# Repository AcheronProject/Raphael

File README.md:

# Acheron Raphael

## Introduction

Raphael is a gummy-mount 60% layout PCB supporting both an on-board USB connector and a JST for USB dautherboard connection.

For its full documentation, see [the AcheronDocs page on Raphael](https://acherondocs.com/pcbs/raphael/raphael)

## Copyright notice

This project is released under the Acheron Open-Hardware License V1.4. For the license, please refer to the LICENCE.md file.

The "angel with sword" logo was licensed through Vectorstock; the license does not allow for redistribution so the source file is not available. The license was obtained in february 08, 2022 and allows for commercial usage of the logo, therefore allowing the PCBs to be used commercially.

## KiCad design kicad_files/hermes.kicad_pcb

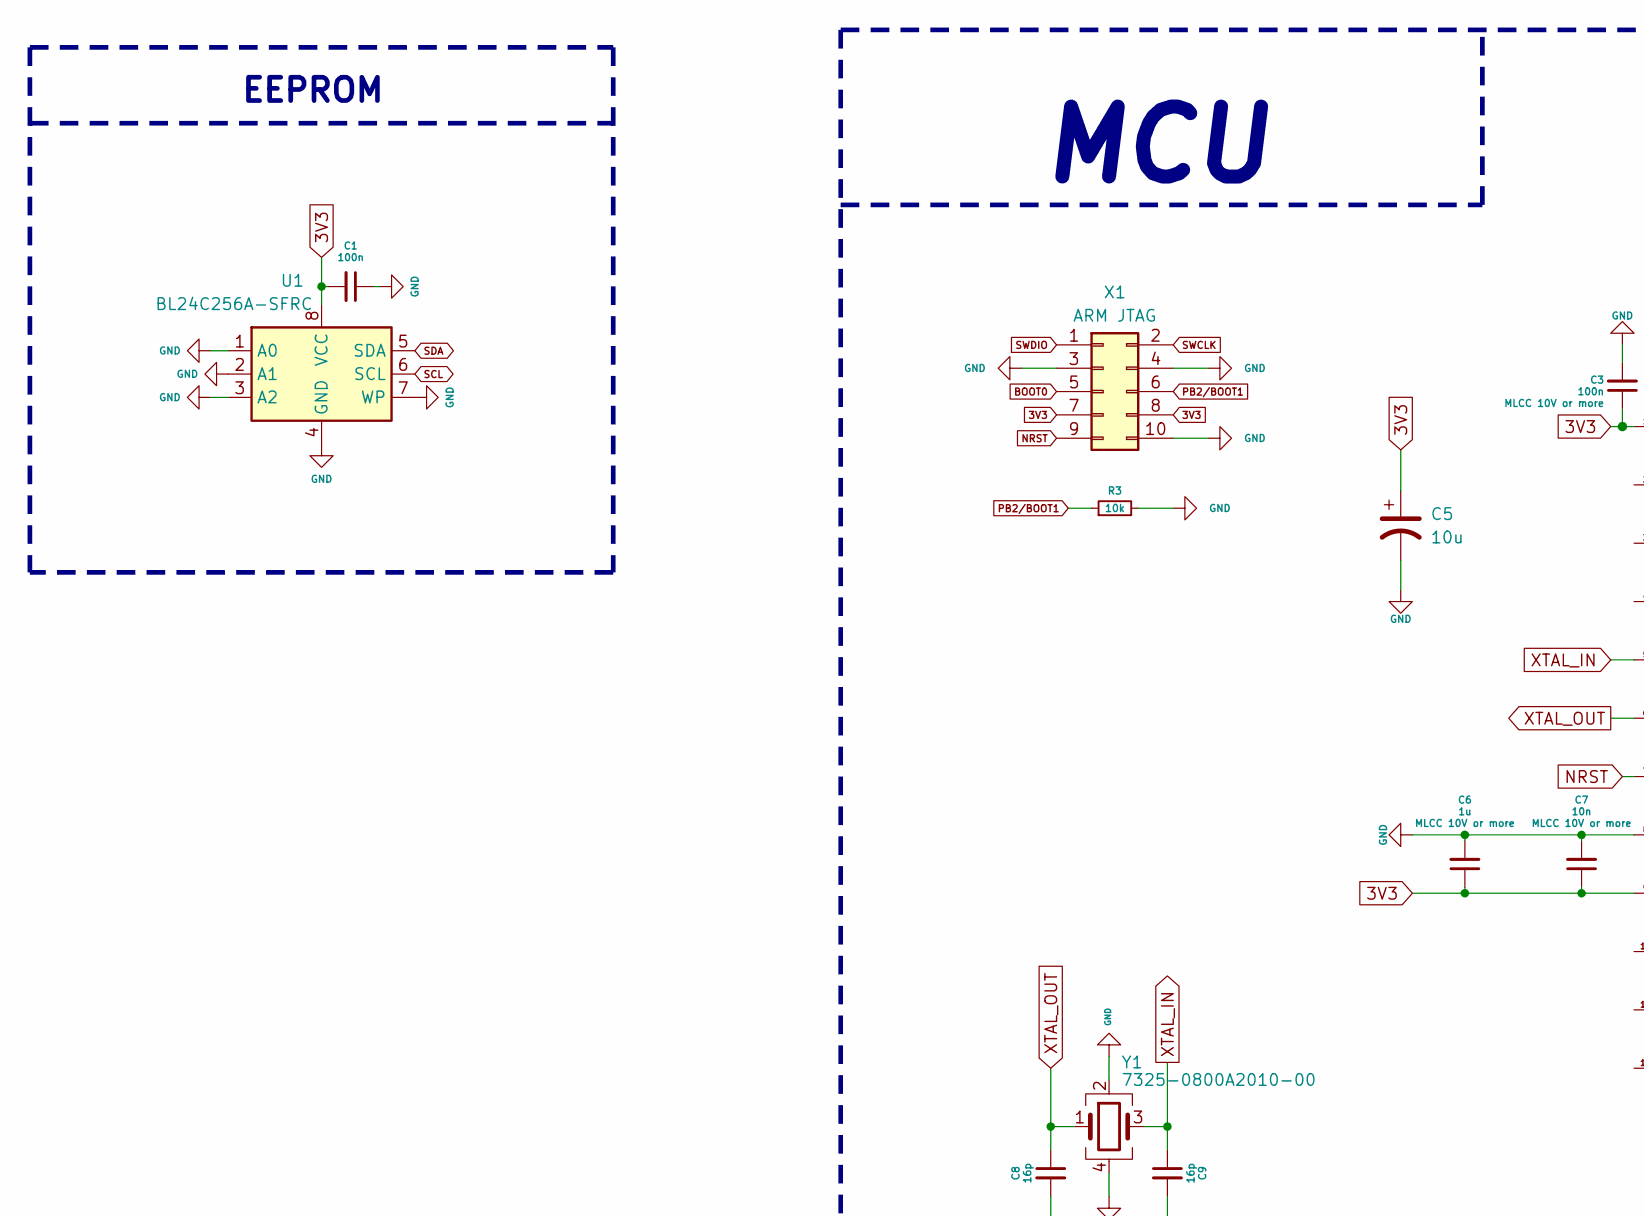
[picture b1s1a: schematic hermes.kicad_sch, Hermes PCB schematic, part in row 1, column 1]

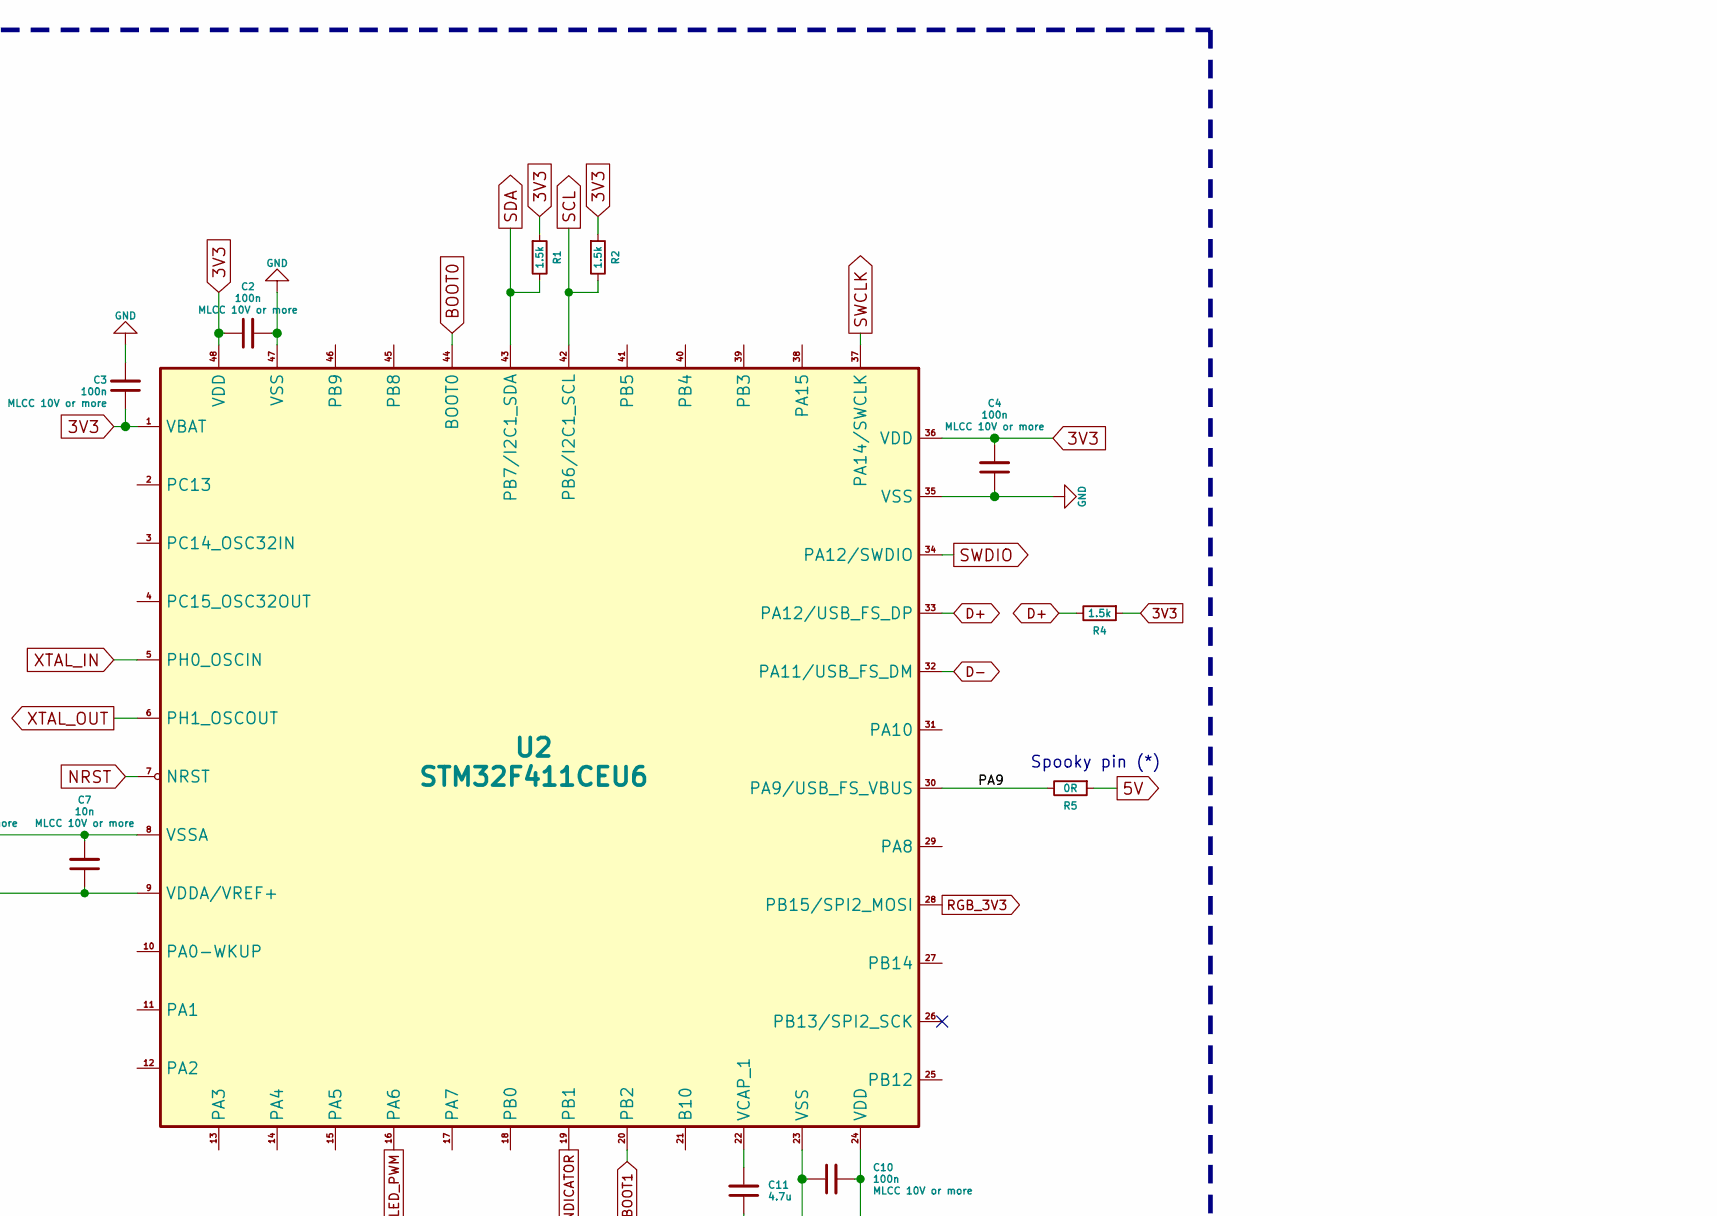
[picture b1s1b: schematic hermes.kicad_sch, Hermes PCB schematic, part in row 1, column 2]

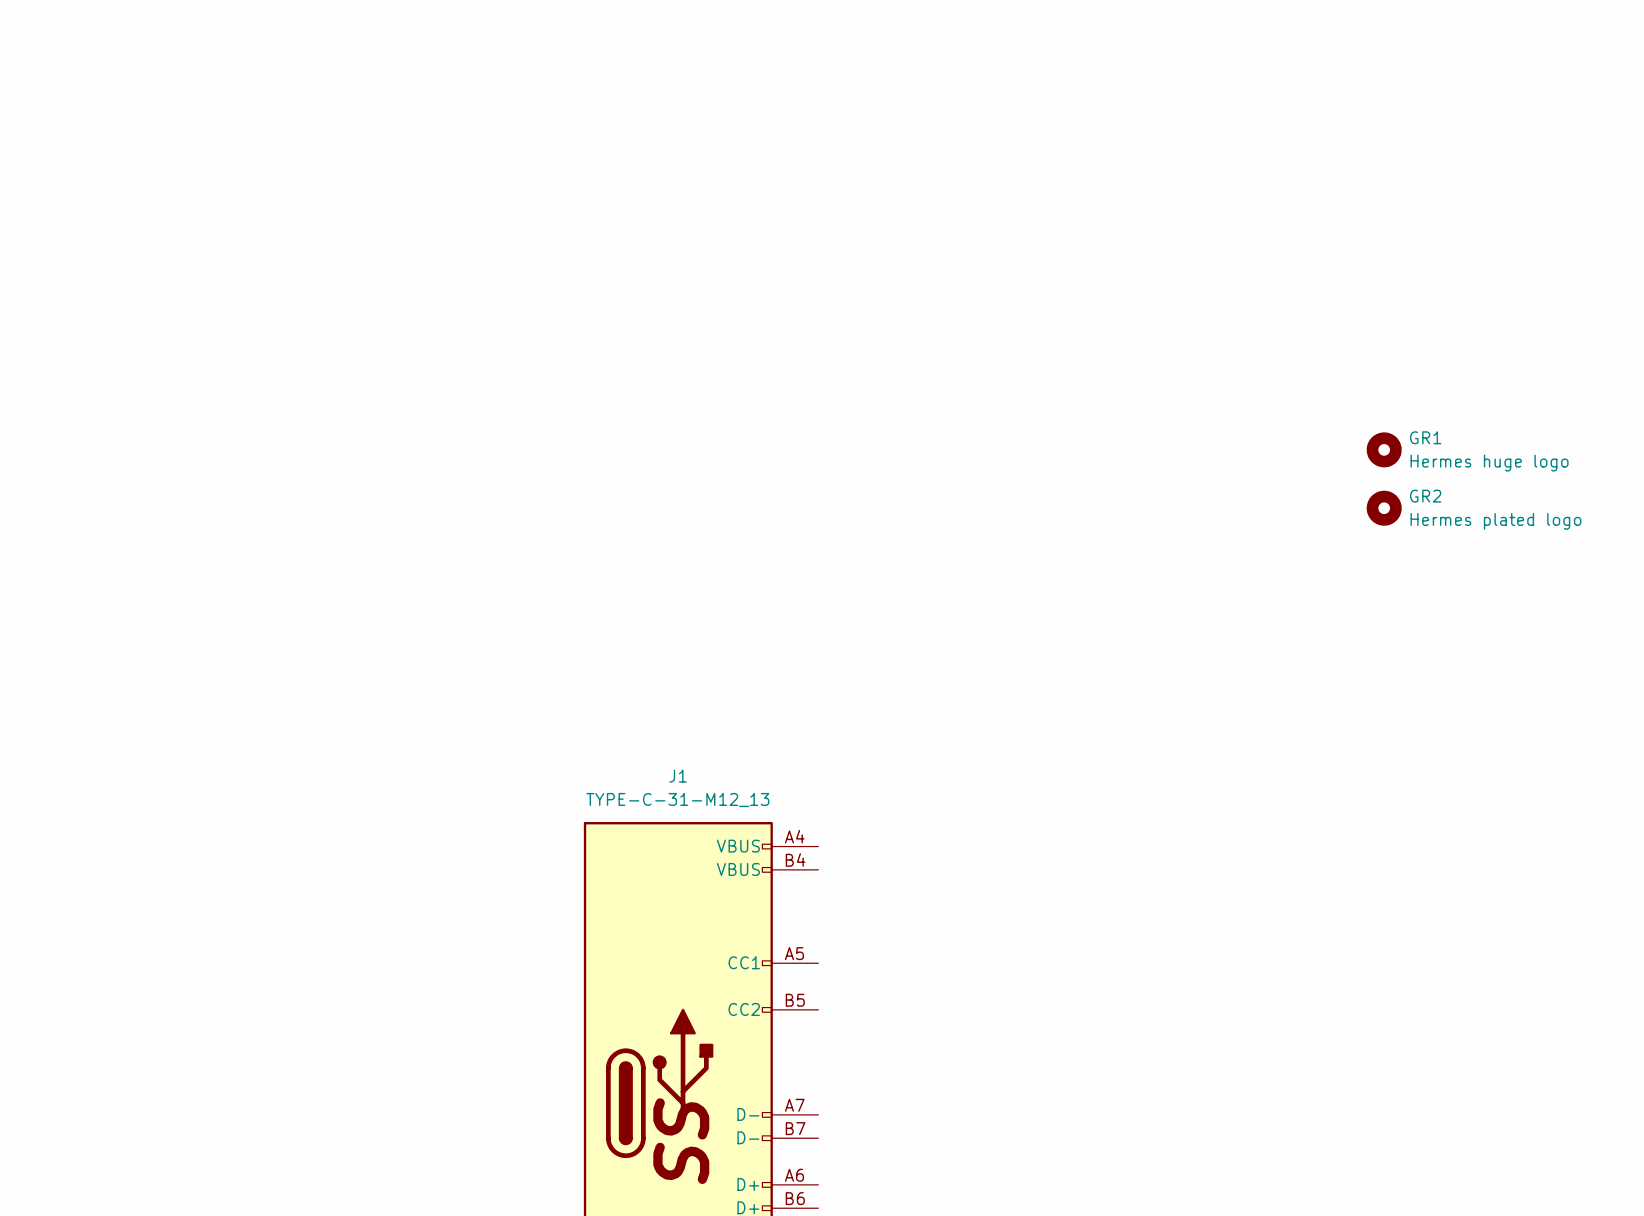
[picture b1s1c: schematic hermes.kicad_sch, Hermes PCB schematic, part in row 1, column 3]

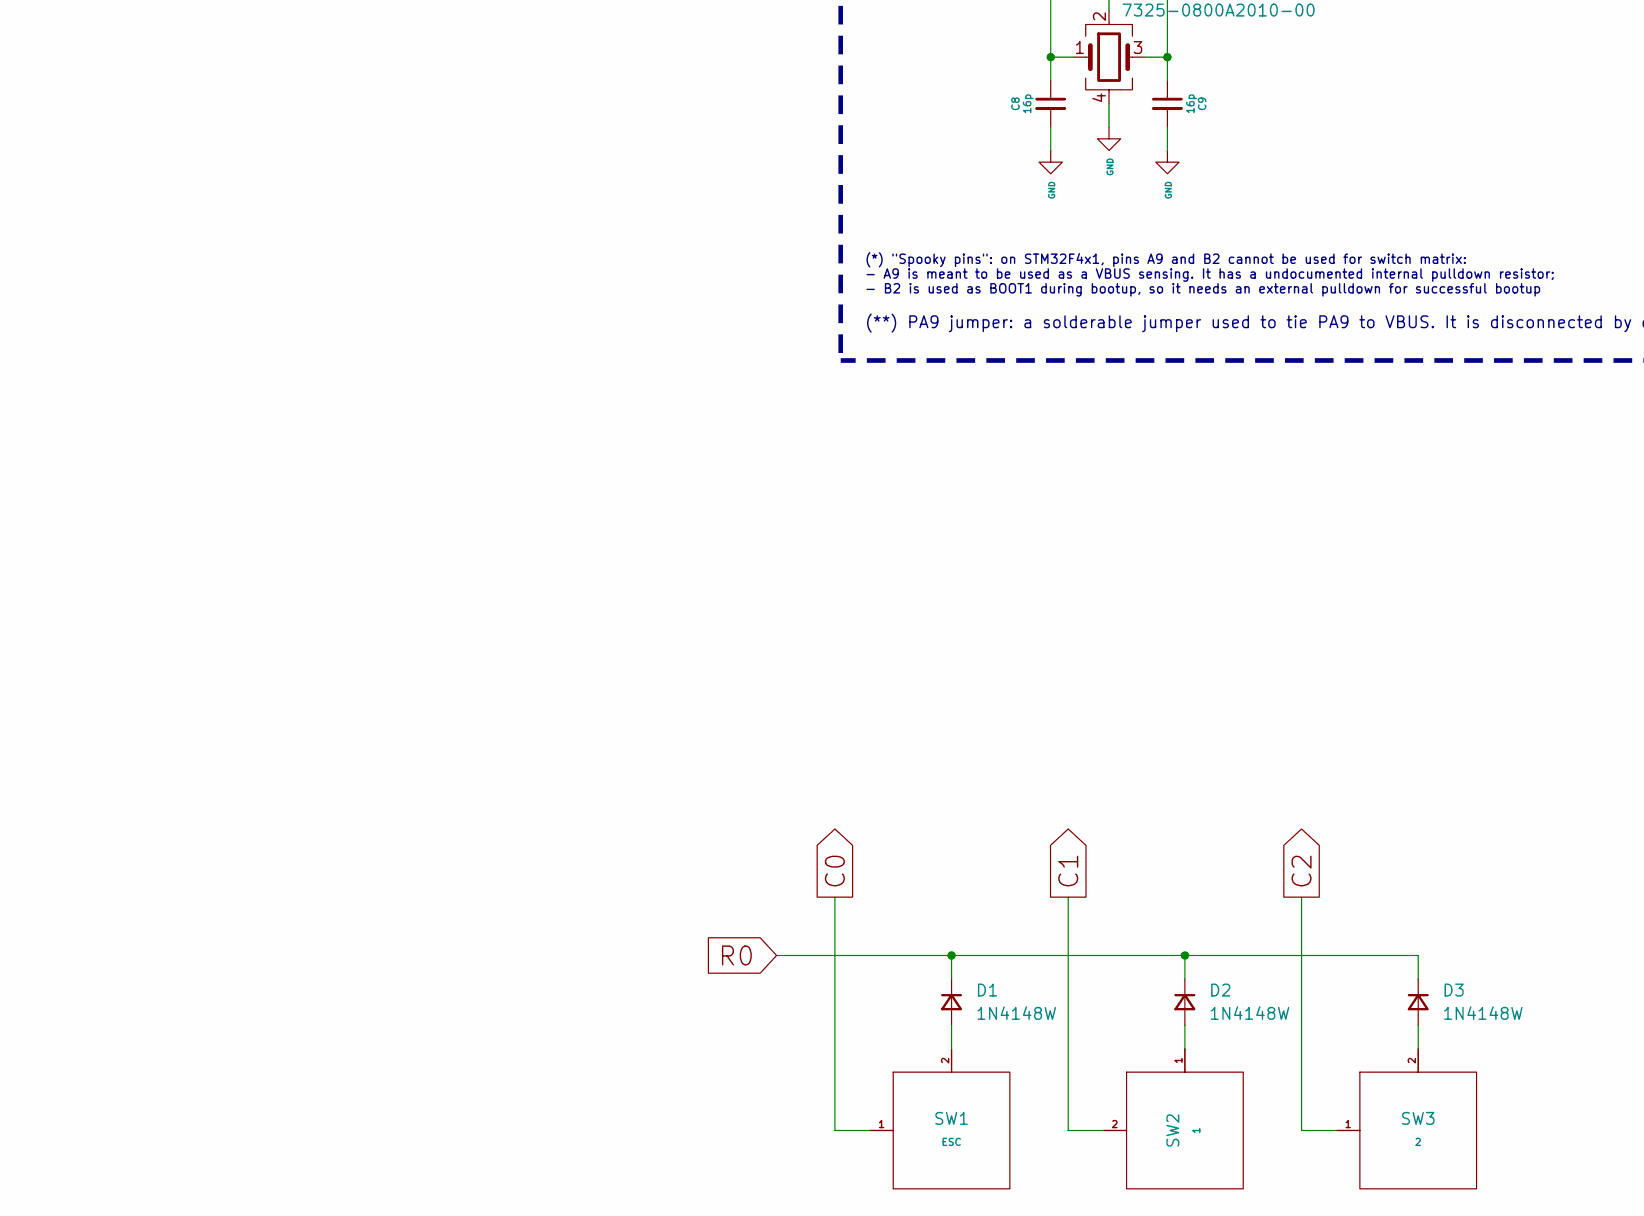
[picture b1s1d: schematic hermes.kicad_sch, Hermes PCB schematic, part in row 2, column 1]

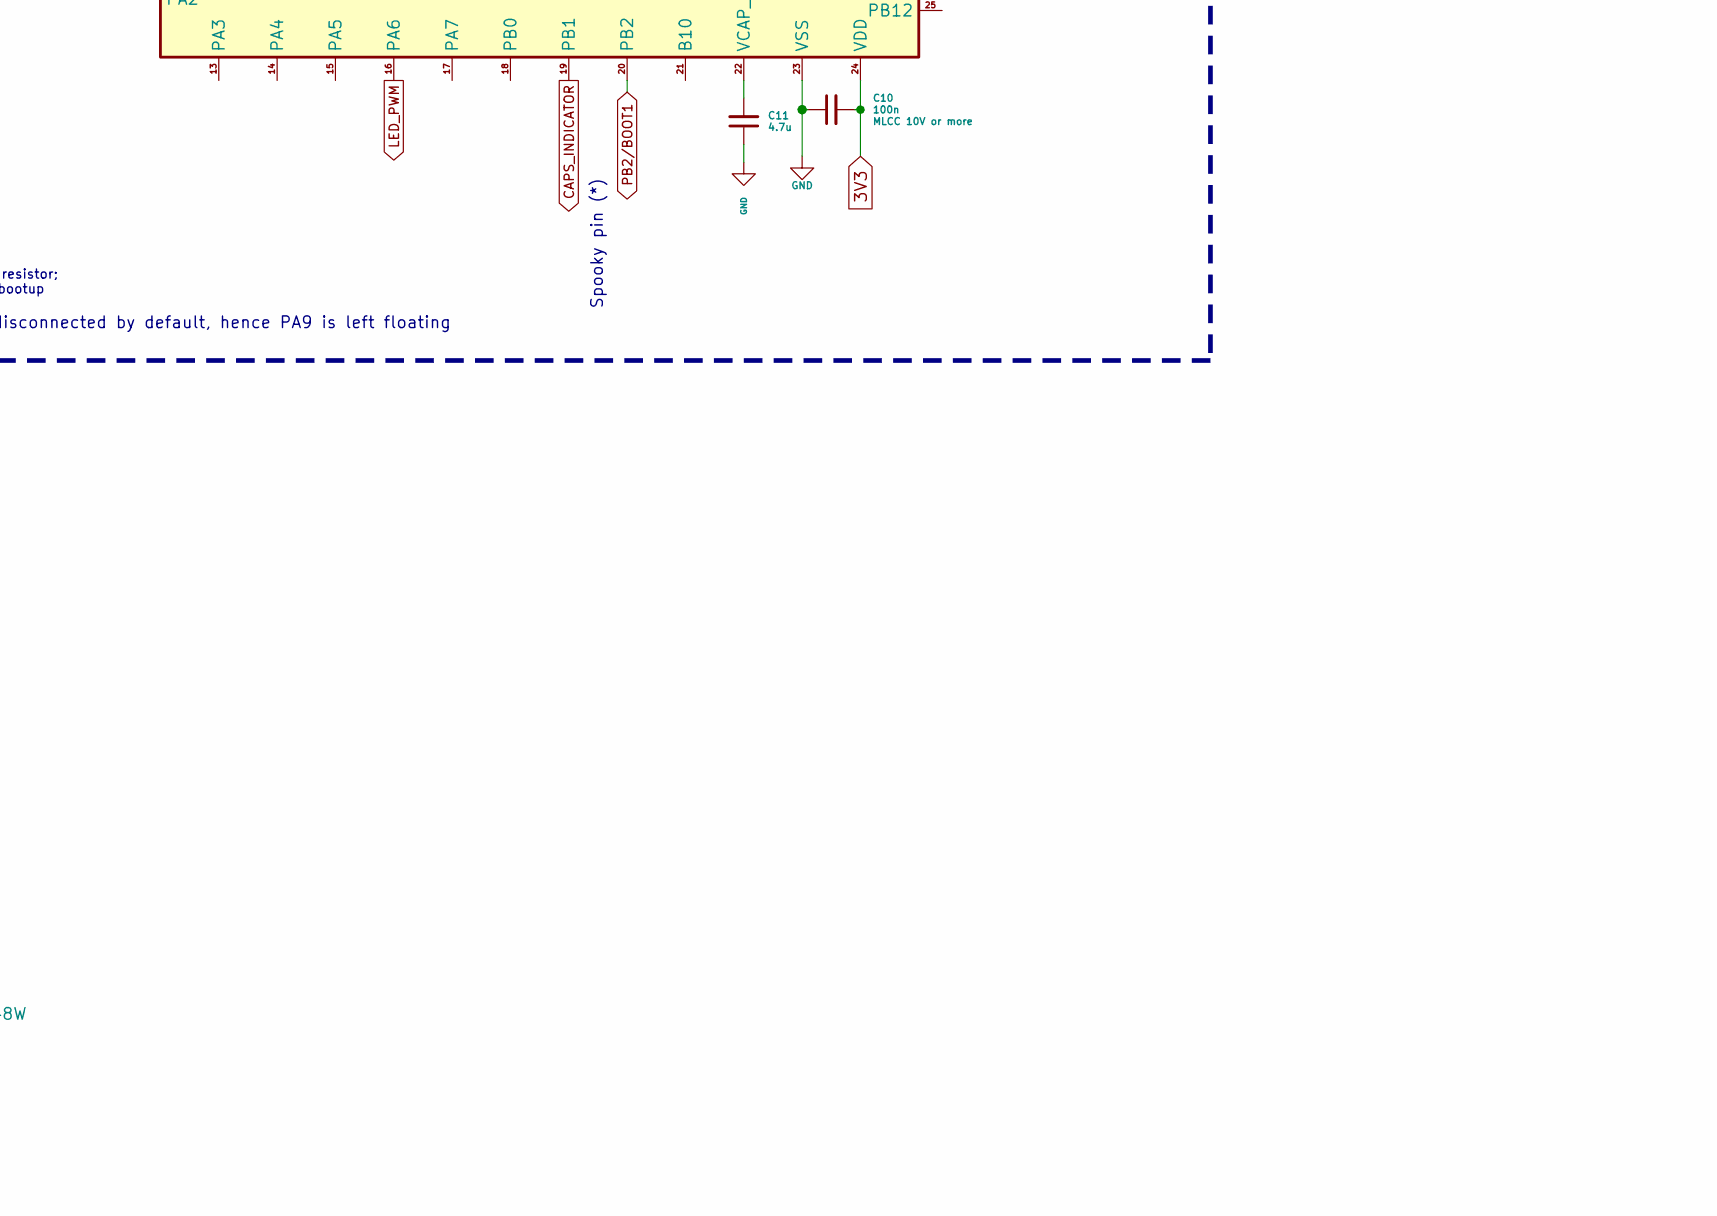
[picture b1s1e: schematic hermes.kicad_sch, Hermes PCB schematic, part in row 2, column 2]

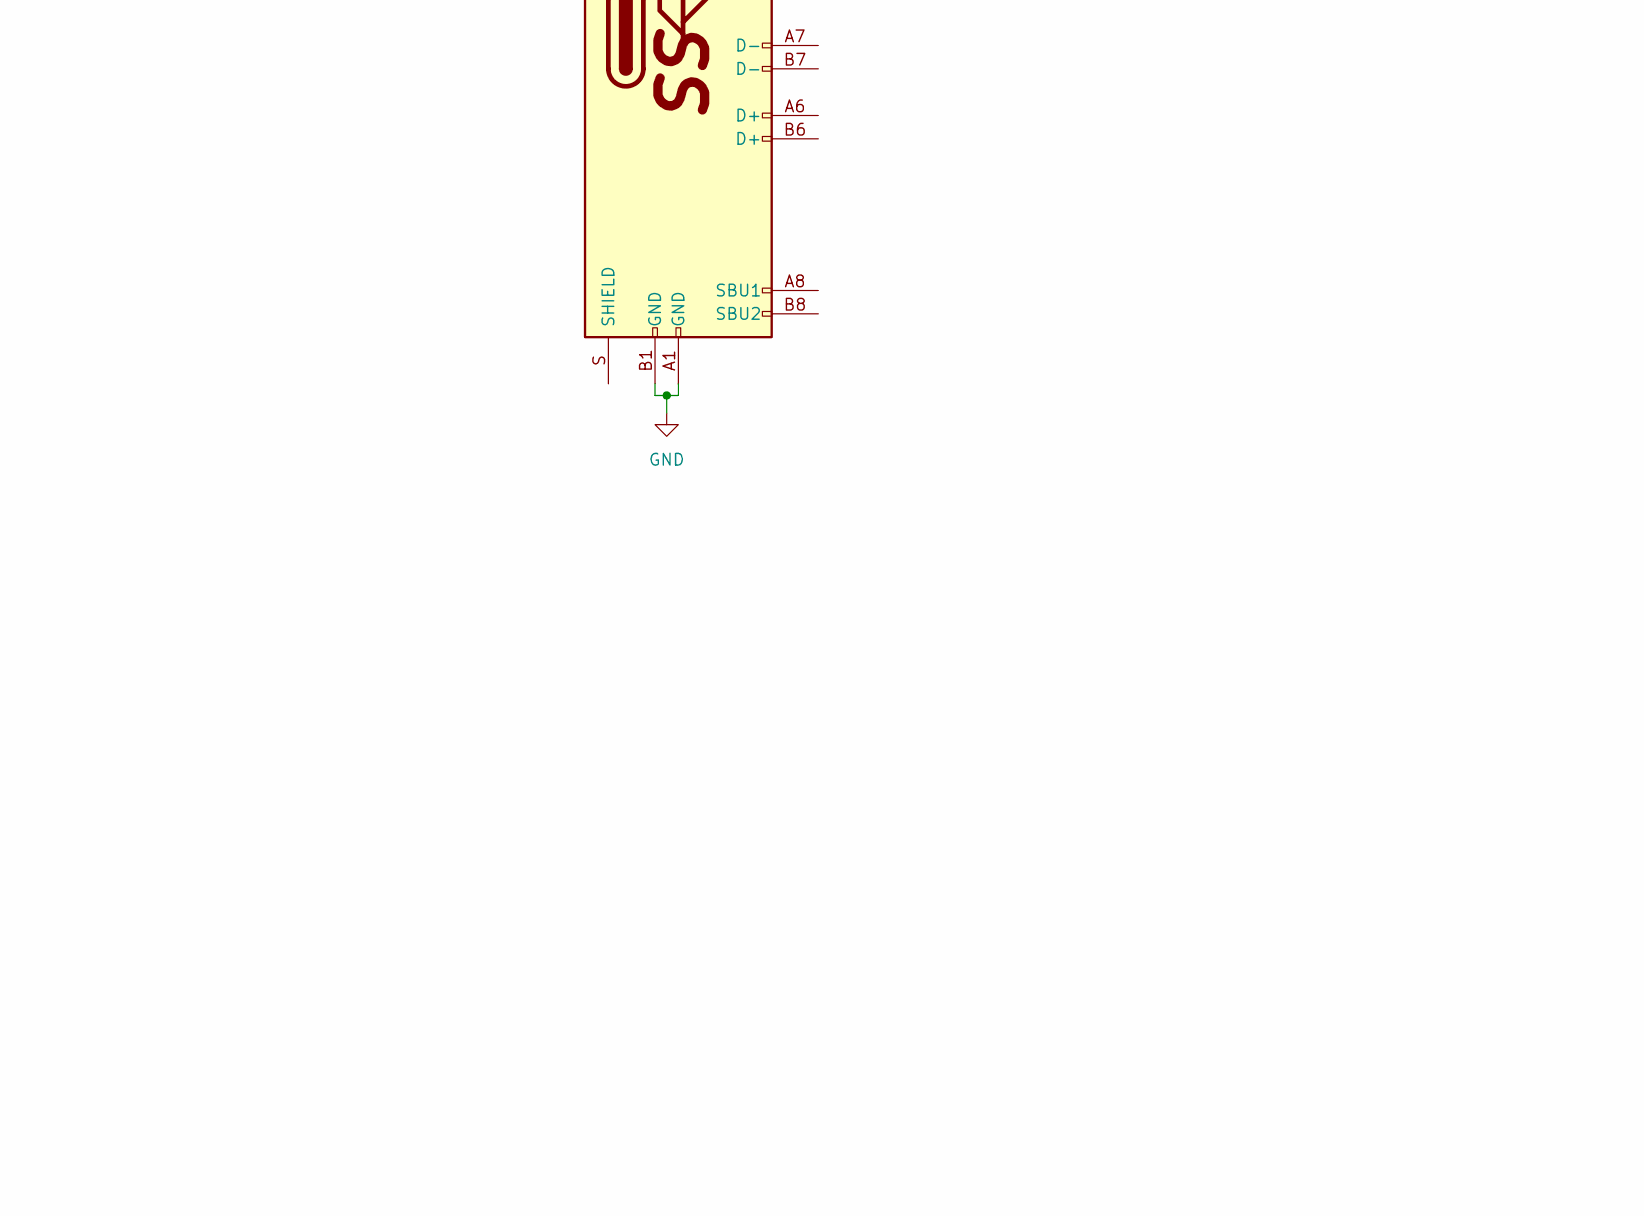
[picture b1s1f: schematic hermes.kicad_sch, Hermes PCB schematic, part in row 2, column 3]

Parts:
C1, C2, C3, C4, C10: 100n; C_0402_1005Metric
C5: 10u; CP_EIA-3216-10_Kemet-I_Pad1.58x1.35mm_HandSolder
C6: 1u; C_0402_1005Metric
C7: 10n; C_0402_1005Metric
C8, C9: 16p; C_0402_1005Metric
C11: 4.7u; C_0402_1005Metric
D1, D2, D3: 1N4148W; D_SOD-123; Manufacturer Part Number 1N4148W
GR1: Hermes huge logo; hermes_logo_56.9x84mm
GR2: Hermes plated logo; hermes_plated_logo_12x17.7mm
J1: TYPE-C-31-M12_13; TYPE-C-31-M-12
R1, R2, R4: 1.5k; R_0402_1005Metric
R3: 10k; R_0805_2012Metric
R5: 0R; R_0805_2012Metric
SW1, SW2, SW3: Mechanical_Switch; MX100
U1: BL24C256A-SFRC; TSSOP-8_4.4x3mm_P0.65mm; Manufacturer Part Number BL24C256A-SFRC
U2: STM32F411CEU6; STM_UFQFPN-48_LQFP-48-1EP_7x7mm_P0.5mm_HandSoldering_Therma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; Manufacturer Part Number STM32F411
X1: ARM JTAG; PinHeader_2x5_P2.54mm_Vertical_Staggered
Y1: 7325-0800A2010-00; Crystal_SMD_3225-4Pin_3.2x2.5mm; Manufacturer Part Number 7325-0800A2010-00

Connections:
3V3: C1.2, C2.1, C3.1, C4.2, C5.1, C6.1, C7.1, C10.2, R1.1, R2.1, R4.1, U1.8 (VCC), U2.1 (VBAT), U2.9 (VDDA/VREF+), U2.24 (VDD), U2.36 (VDD), U2.48 (VDD), X1.7, X1.8
5V: R5.1
/PA9: R5.2, U2.30 (PA9/USB_FS_VBUS)
BOOT0: U2.44 (BOOT0), X1.5
C0: SW1.1
C1: SW2.2
C2: SW3.1
CAPS_INDICATOR: U2.19 (PB1)
D+: R4.2, U2.33 (PA12/USB_FS_DP)
D-: U2.32 (PA11/USB_FS_DM)
GND: C1.1, C2.2, C3.2, C4.1, C5.2, C6.2, C7.2, C8.2, C9.2, C10.1, C11.1, J1.A1 (GND), J1.B1 (GND), R3.2, U1.1 (A0), U1.2 (A1), U1.3 (A2), U1.4 (GND), U1.7 (WP), U2.8 (VSSA), U2.23 (VSS), U2.35 (VSS), U2.47 (VSS), X1.3, X1.4, X1.10, Y1.2, Y1.4
LED_PWM: U2.16 (PA6)
NRST: U2.7 (NRST), X1.9
unnamed: C11.2, U2.22 (VCAP_1)
unnamed: D1.2 (A), SW1.2
unnamed: D2.2 (A), SW2.1
unnamed: D3.2 (A), SW3.2
PB2/BOOT1: R3.1, U2.20 (PB2), X1.6
R0: D1.1 (K), D2.1 (K), D3.1 (K)
RGB_3V3: U2.28 (PB15/SPI2_MOSI)
SCL: R2.2, U1.6 (SCL), U2.42 (PB6/I2C1_SCL)
SDA: R1.2, U1.5 (SDA), U2.43 (PB7/I2C1_SDA)
SWCLK: U2.37 (PA14/SWCLK), X1.2
SWDIO: U2.34 (PA12/SWDIO), X1.1
XTAL_IN: C9.1, U2.5 (PH0_OSCIN), Y1.3
XTAL_OUT: C8.1, U2.6 (PH1_OSCOUT), Y1.1

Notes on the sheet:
Spooky pin (*)
(*) "Spooky pins": on STM32F4x1, pins A9 and B2 cannot be used for switch matrix: - A9 is meant to be used as a VBUS sensing. It has a undocumented internal pulldown resistor; - B2 is used as BOOT1 during bootup, so it needs an external pulldown for successful bootup
MCU
EEPROM
(**) PA9 jumper: a solderable jumper used to tie PA9 to VBUS. It is disconnected by default, hence PA9 is left floating

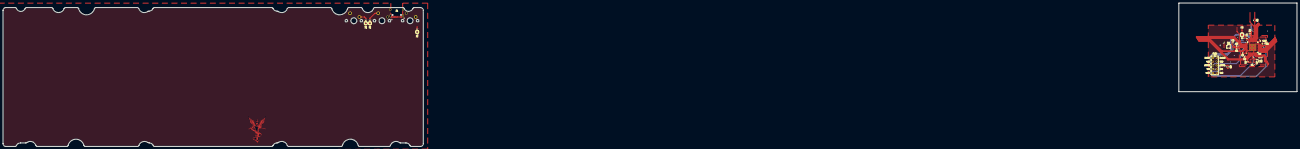
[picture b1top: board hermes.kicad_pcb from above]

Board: 2 copper layers, 876.1 x 97.1 mm, 29 parts (1 on the bottom side), 18 nets.

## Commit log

2022-02-09 Placing switches
2022-02-17 Name change to Raphael, move MCU and add RAPHAEL letters
2022-02-18 Place diodes and LEDs
2022-02-18 Finish routing; DRC pending
2022-04-09 Reset circuit, QoL
    - Reset circuit was updated with a single-package double MOSFET 2N7002DW
    - Quality of life tracing improvements
2022-04-09 Rename files to Raphael
2022-04-09 Add label
2022-04-10 Organize schematic, preparing for release
2022-04-10 Edit metadata, release
2022-04-10 Add KLE resources
2022-04-10 Edit component metadata
2022-05-04 Add KLE and VIA
